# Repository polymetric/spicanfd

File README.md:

# spicanfd
Add a CAN-FD interface to a microcontroller through SPI. Uses the MCP2517FD chip + ATA6561 transceiver.

Based on [Longan Labs' CAN FD Shield](https://github.com/Longan-Labs/Longan_Labs_CAN_FD_Eagle/) for the Arduino Uno. It's basically a breakout board form of that. Their shield is nicer to use but this board is a lot cheaper to fab since it's smaller and has less components.

For usage, please refer to the [MCP2517FD datasheet](https://ww1.microchip.com/downloads/en/DeviceDoc/MCP2517FD-External-CAN-FD-Controller-with-SPI-Interface-20005688B.pdf) and the [acan2517FD](https://github.com/pierremolinaro/acan2517FD) Arduino library.

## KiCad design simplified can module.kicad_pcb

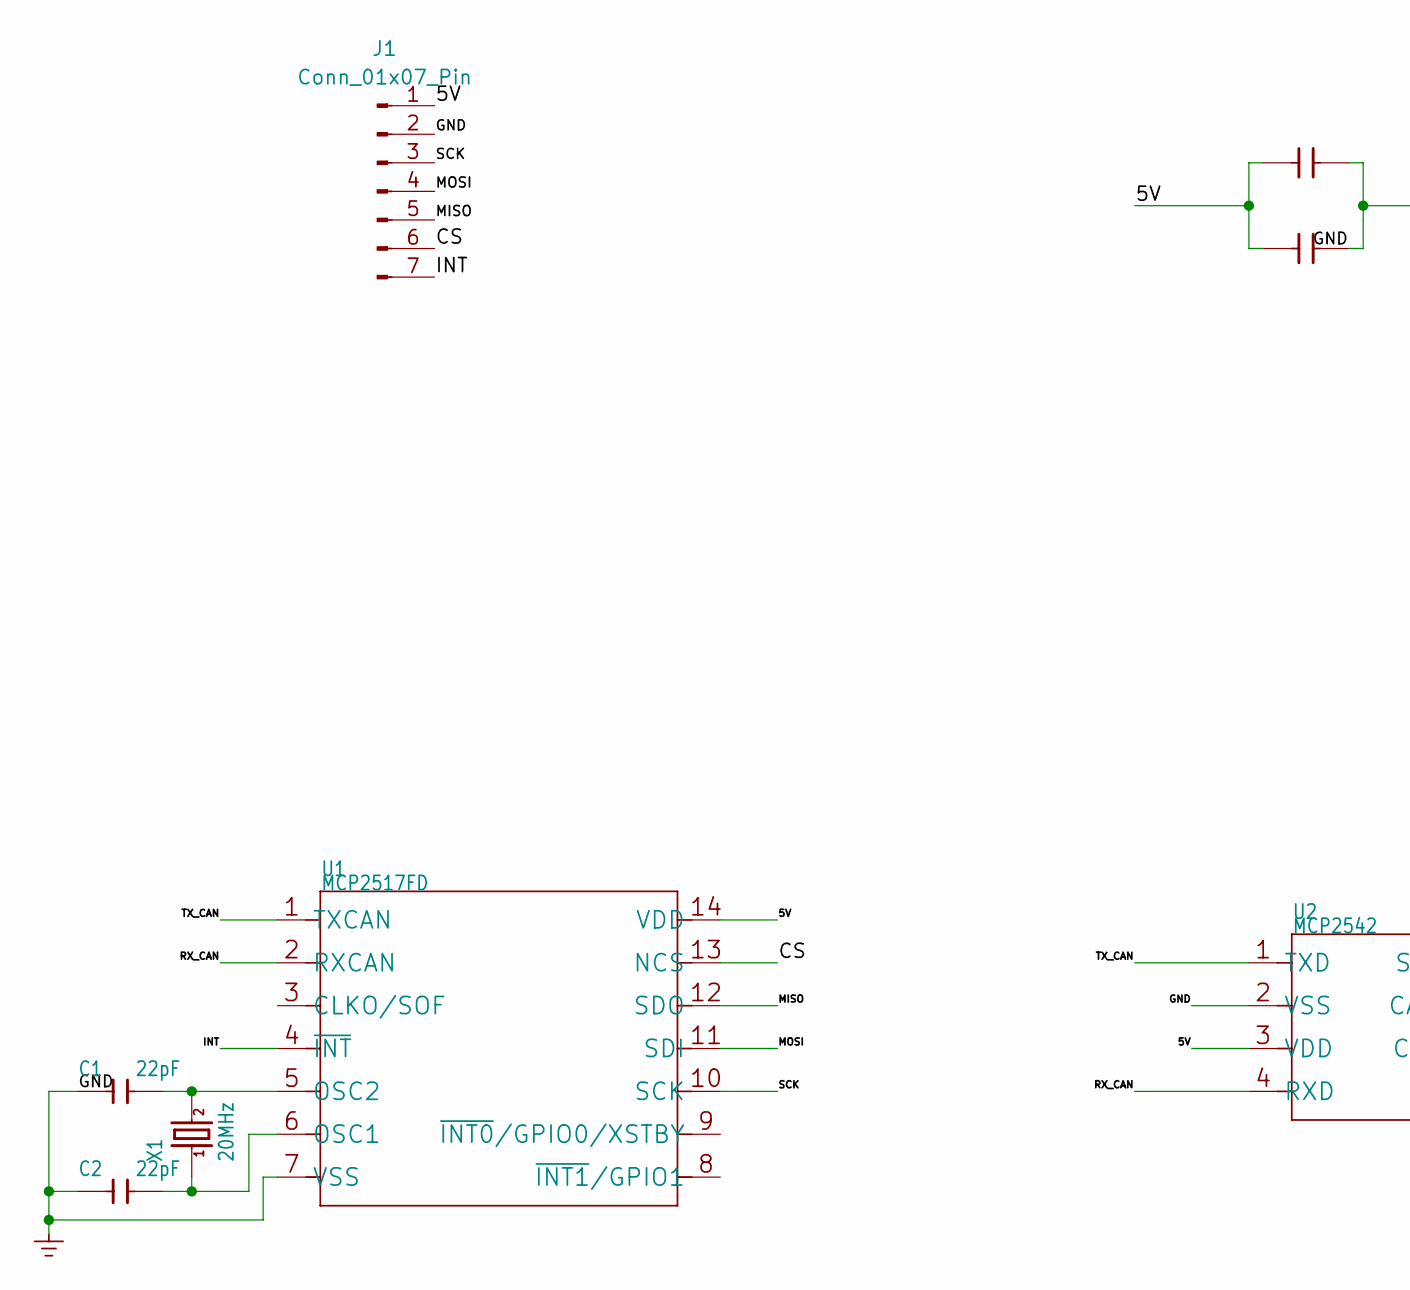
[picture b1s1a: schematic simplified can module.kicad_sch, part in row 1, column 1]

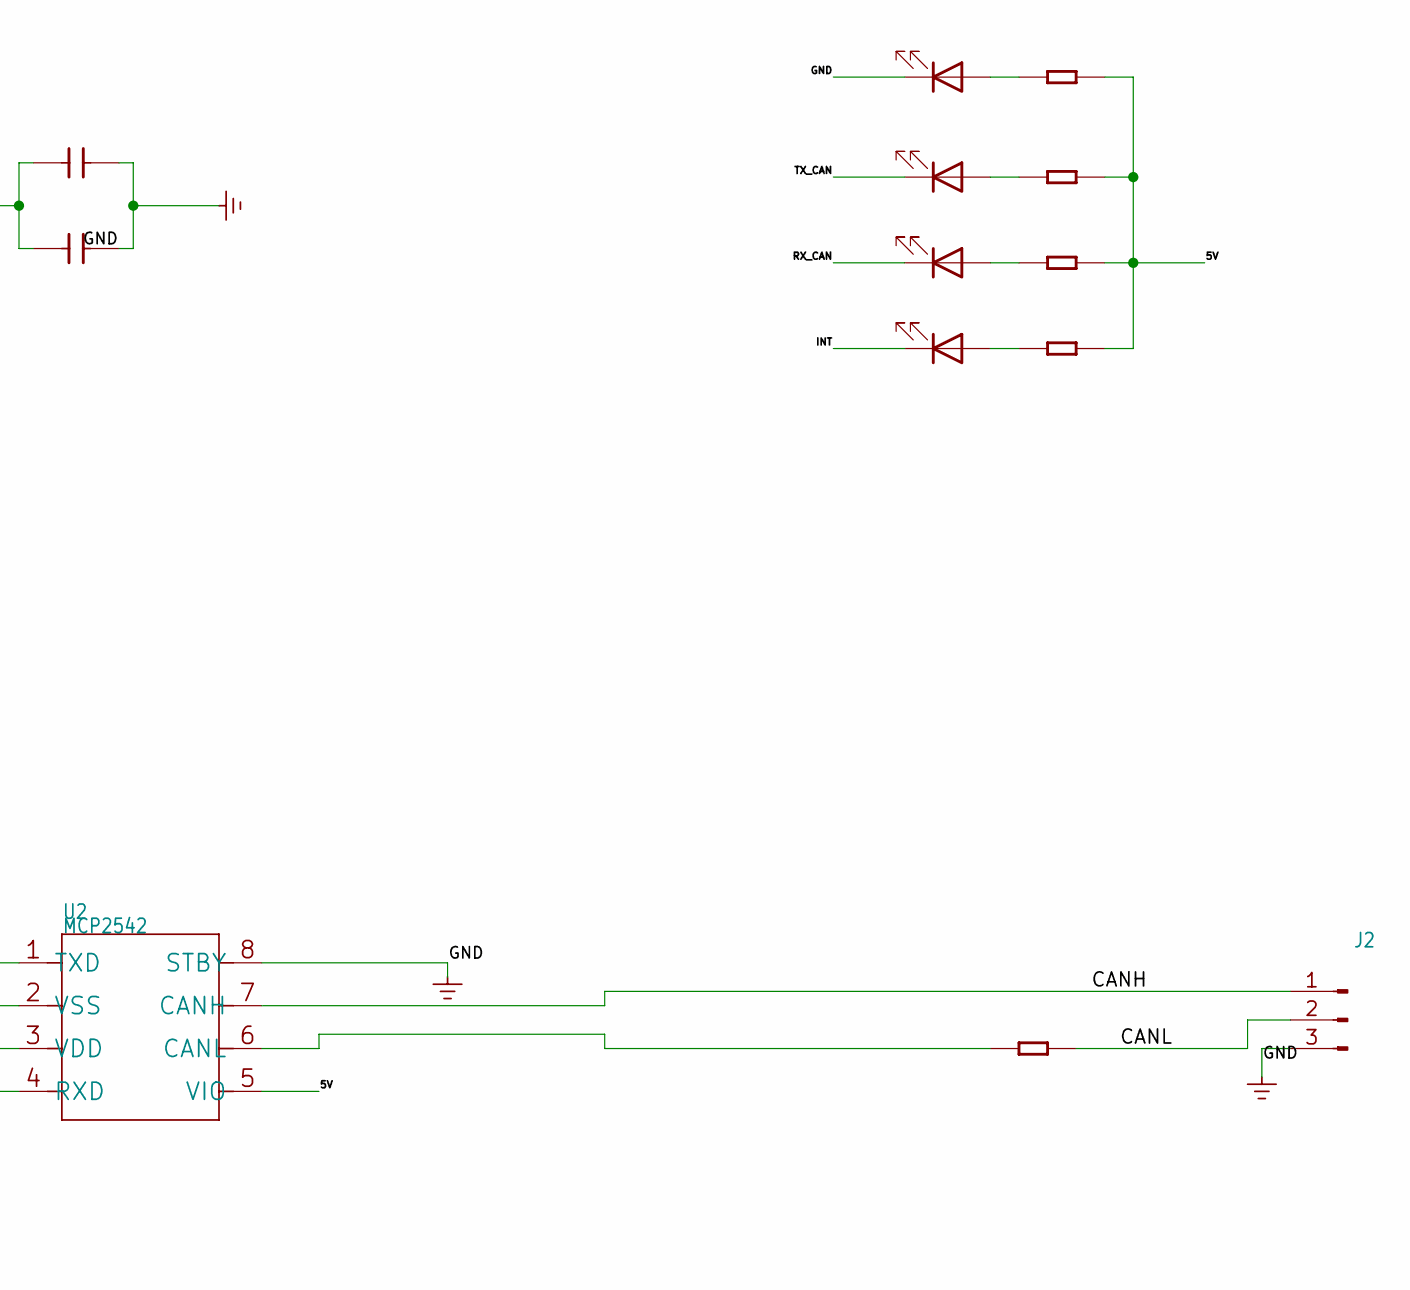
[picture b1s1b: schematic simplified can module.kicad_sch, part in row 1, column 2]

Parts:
C1, C2: 22pF; C_0603_1608Metric
C3, C4: 100nF; C_0603_1608Metric
INT1: RED; LED_0603_1608Metric
J1: Conn_01x07_Pin; PinHeader_1x07_P2.54mm_Vertical
J2: SCREW-TERMINAL-2P'5.08'; PinHeader_1x03_P2.54mm_Vertical
PWR1: GREEN; LED_0603_1608Metric
R1: 120R; R_0603_1608Metric
R2, R3, R4, R5: 1k; R_0603_1608Metric
RX1: RED; LED_0603_1608Metric
TX1: RED; LED_0603_1608Metric
U1: MCP2517FD; SOIC-14_3.9x8.7mm_P1.27mm
U2: MCP2542; SOIC-8_3.9x4.9mm_P1.27mm
X1: 20MHz; Crystal_SMD_HC49-SD

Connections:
/5V: C3.1, C4.1, J1.1, R2.2, R3.2, R4.2, R5.2, U1.14 (VDD), U2.3 (VDD), U2.5 (VIO)
/CANH: J2.1, U2.7 (CANH)
/CANL: J2.2, R1.2
/CS: J1.6, U1.13 (NCS)
/INT: INT1.1 (K), J1.7, U1.4 (~INT)
/MISO: J1.5, U1.12 (SDO)
/MOSI: J1.4, U1.11 (SDI)
/RX_CAN: RX1.1 (K), U1.2 (RXCAN), U2.4 (RXD)
/SCK: J1.3, U1.10 (SCK)
/TX_CAN: TX1.1 (K), U1.1 (TXCAN), U2.1 (TXD)
GND_POWER: C1.1, C2.1, C3.2, C4.2, J1.2, J2.3, PWR1.1 (K), U1.7 (VSS), U2.2 (VSS), U2.8 (STBY)
unnamed: INT1.2 (A), R5.1
unnamed: PWR1.2 (A), R2.1
unnamed: R4.1, RX1.2 (A)
unnamed: R3.1, TX1.2 (A)
unnamed: C2.2, U1.6 (OSC1), X1.1
unnamed: C1.2, U1.5 (OSC2), X1.2
unnamed: R1.1, U2.6 (CANL)

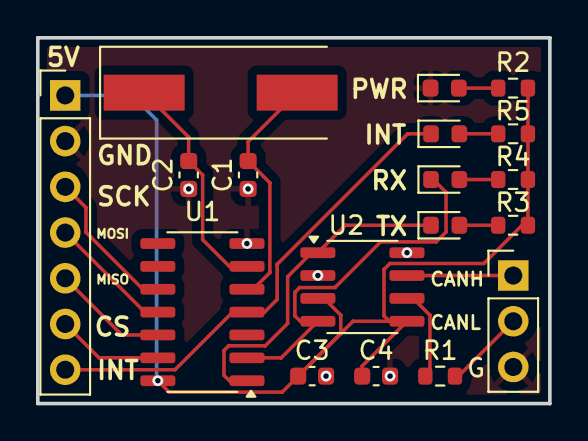
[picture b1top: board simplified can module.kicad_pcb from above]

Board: 2 copper layers, 28.4 x 20.3 mm, 18 parts (0 on the bottom side), 18 nets.

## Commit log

2025-05-28 move fab labels and add bom
2025-05-28 add license, readme and gitignore
2025-05-28 add kicad 3d image
2025-05-29 add CAN pin labels
    also:
    - reduced thermal relief spoke size to help soldering
    - changed solder mask color to purple in 3d renderer
2025-05-29 update CAN header labels
2025-06-09 add copyright and version info

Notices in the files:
simplified can module.kicad_pcb:
copyright (c) 2025 Eli Rutan
